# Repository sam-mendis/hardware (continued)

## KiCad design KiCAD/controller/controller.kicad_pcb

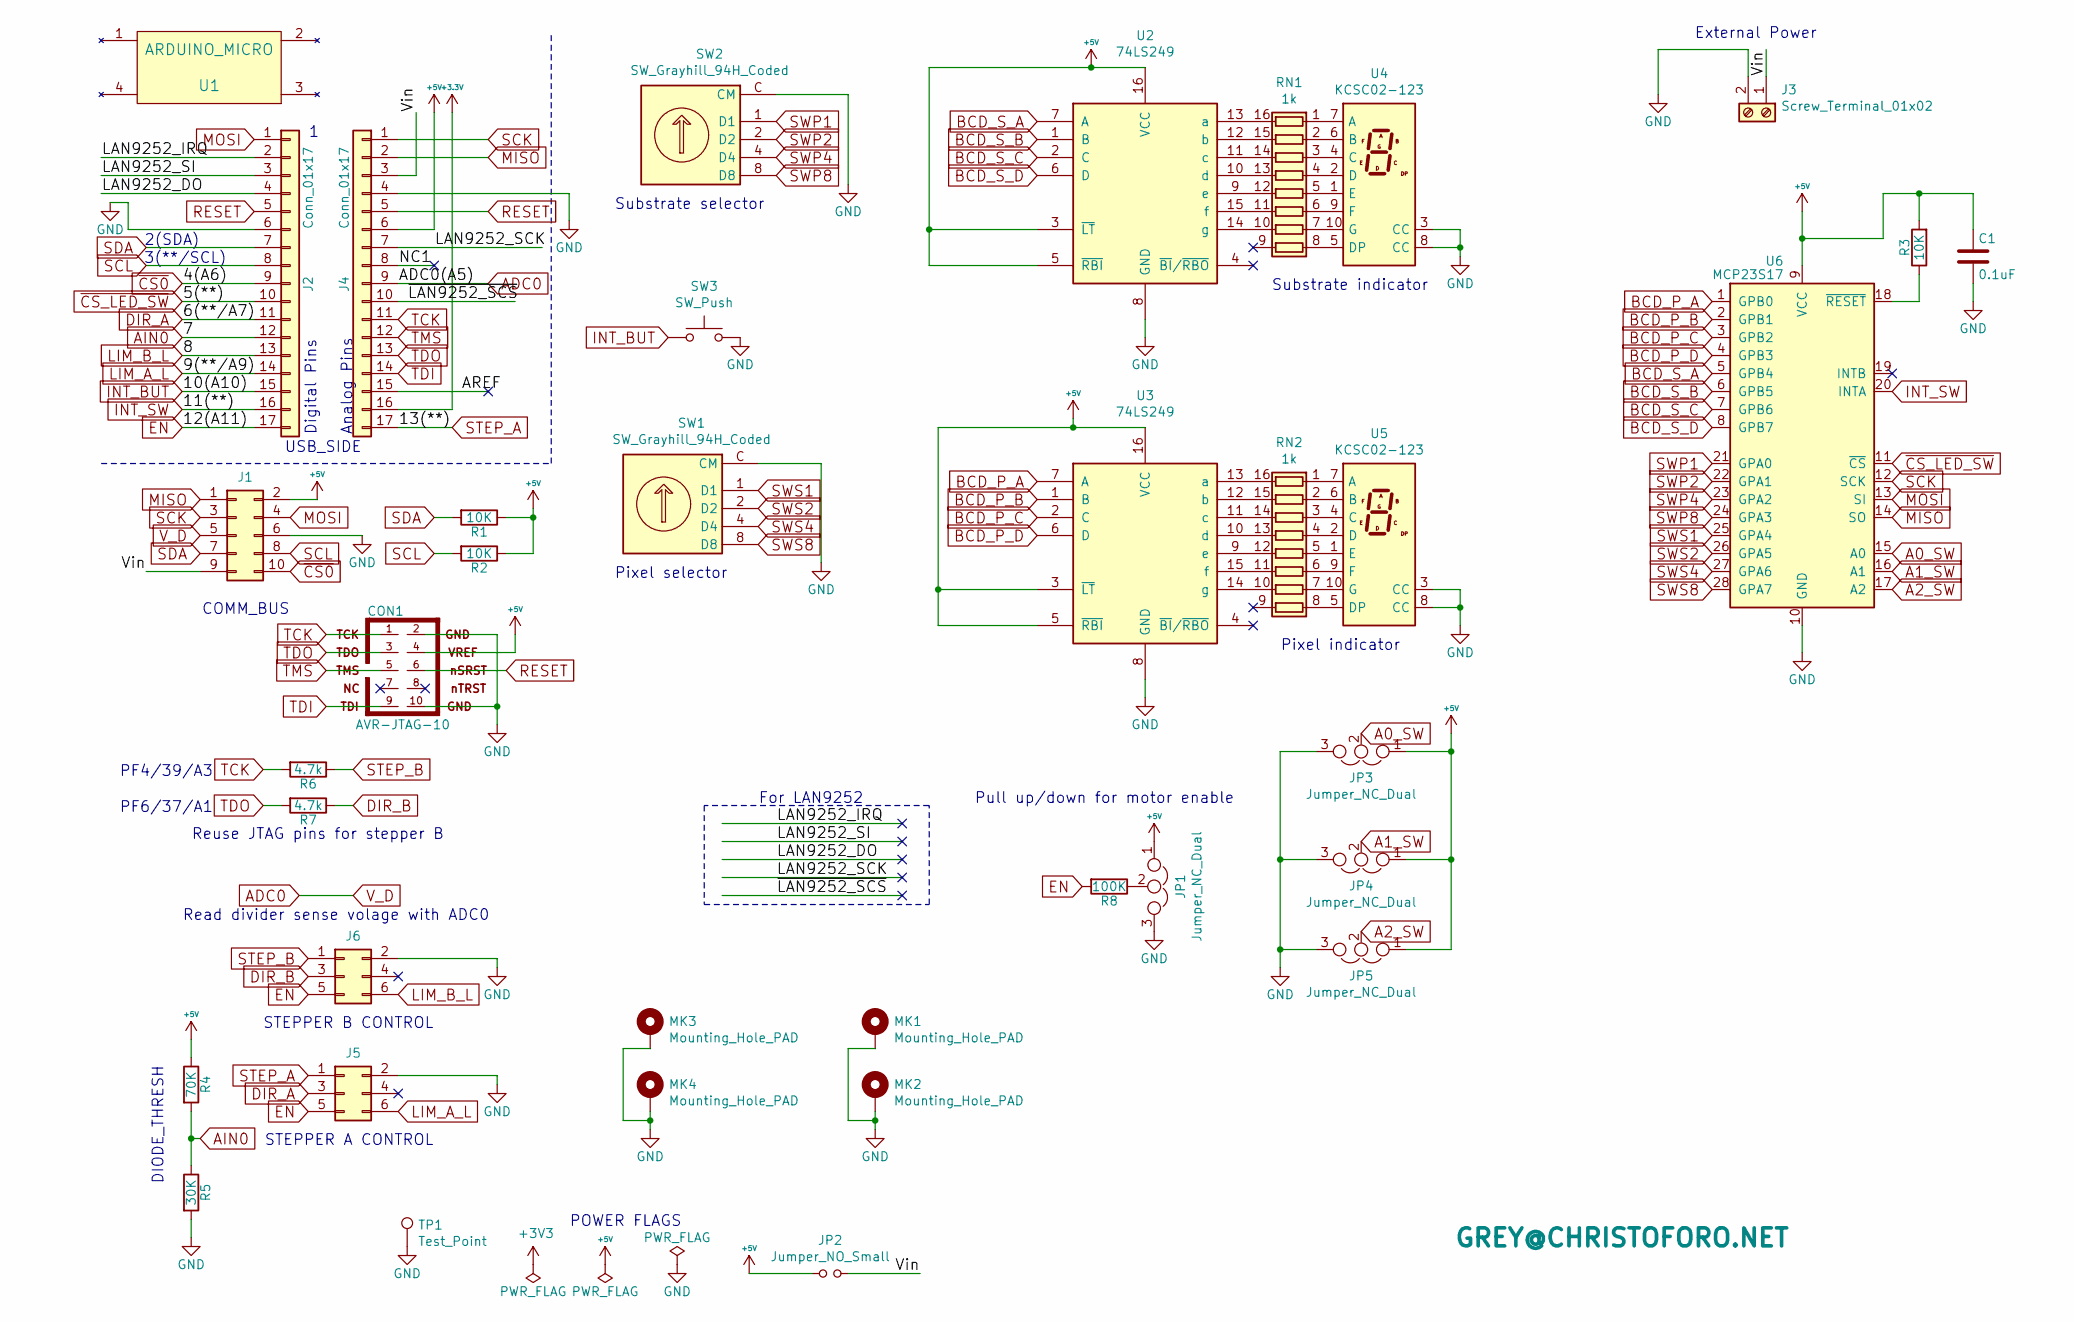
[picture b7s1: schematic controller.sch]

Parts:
C1: 0.1uF; C_0805_HandSoldering
CON1: AVR-JTAG-10; Multicomp_MC9A12-1034_2x05x2.54mm_Straight
J1: Conn_02x05_Counter_Clockwise; Pin_Header_Angled_2x05_Pitch2.54mm
J2, J4: Conn_01x17; Socket_Strip_Straight_1x17_Pitch2.54mm
J3: Screw_Terminal_01x02; PhoenixContact_MC-GF_02x3.50mm_Angled_ThreadedFlange_MountH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
J5, J6: Conn_02x03_Odd_Even; Pin_Header_Angled_2x03_Pitch2.54mm
JP1, JP3, JP4, JP5: Jumper_NC_Dual; GS3
JP2: Jumper_NO_Small; GS2
L1: GREY@CHRISTOFORO.NET; logo
MK1, MK2, MK3, MK4: Mounting_Hole_PAD; MountingHole_2.2mm_M2_Pad
R1, R2, R3: 10K; R_0805_HandSoldering
R4: 70K; R_0805_HandSoldering
R5: 30K; R_0805_HandSoldering
R6, R7: 4.7k; R_0805_HandSoldering
R8: 100K; R_0805_HandSoldering
RN1, RN2: 1k; DIP-16_W7.62mm
SW1, SW2: SW_Grayhill_94H_Coded; Grayhill_94H; farnellCode 1608126+1082532
SW3: SW_Push; SW_PUSH_6mm
TP1: Test_Point; Test_Point_S1751-46R
U1: ARDUINO_MICRO; arduino_micro
U2, U3: 74LS249; DIP-16_W7.62mm
U4, U5: KCSC02-123
U6: MCP23S17; DIP-28_W7.62mm

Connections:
+5V: C1.1, CON1.4, J1.2, J4.6, JP1.1, JP2.1, JP3.1, JP4.1, JP5.1, R1.1, R2.1, R3.2, R4.1, U2.3 (~LT), U2.5 (~RBI), U2.16 (VCC), U3.3 (~LT), U3.5 (~RBI), U3.16 (VCC), U6.9 (VCC)
/LAN9252_DO: J2.4
/LAN9252_IRQ: J2.2
/LAN9252_SCK: J4.7
/LAN9252_SI: J2.3
/Vin: J1.9, J3.1, J4.3, JP2.2
/~LAN9252_SCS: J4.10
A0_SW: JP3.2, U6.15 (A0)
A1_SW: JP4.2, U6.16 (A1)
A2_SW: JP5.2, U6.17 (A2)
ADC0: J1.5, J4.9
AIN0: J2.12, R4.2, R5.1
BCD_P_A: U3.7 (A), U6.1 (GPB0)
BCD_P_B: U3.1 (B), U6.2 (GPB1)
BCD_P_C: U3.2 (C), U6.3 (GPB2)
BCD_P_D: U3.6 (D), U6.4 (GPB3)
BCD_S_A: U2.7 (A), U6.5 (GPB4)
BCD_S_B: U2.1 (B), U6.6 (GPB5)
BCD_S_C: U2.2 (C), U6.7 (GPB6)
BCD_S_D: U2.6 (D), U6.8 (GPB7)
DIR_A: J2.11, J5.3
DIR_B: J6.3, R7.1
EN: J2.17, J5.5, J6.5, R8.2
GND: C1.2, CON1.2, CON1.10, J1.6, J2.6, J3.2, J4.4, J5.2, J6.2, JP1.3, JP3.3, JP4.3, JP5.3, MK1.1, MK2.1, MK3.1, MK4.1, R5.2, SW1.C (CM), SW2.C (CM), SW3.2, TP1.1, U2.8 (GND), U3.8 (GND), U4.3 (CC), U4.8 (CC), U5.3 (CC), U5.8 (CC), U6.10 (GND)
INT_BUT: J2.15, SW3.1
INT_SW: J2.16, U6.20 (INTA)
LIM_A_L: J2.14, J5.6
LIM_B_L: J2.13, J6.6
MISO: J1.1, J4.2, U6.14 (SO)
MOSI: J1.4, J2.1, U6.13 (SI)
unnamed: JP1.2, R8.1
unnamed: R3.1, U6.18 (~RESET)
unnamed: RN1.1 (R1.1), U4.7 (A)
unnamed: RN1.2 (R2.1), U4.6 (B)
unnamed: RN1.3 (R3.1), U4.4 (C)
unnamed: RN1.4 (R4.1), U4.2 (D)
unnamed: RN1.5 (R5.1), U4.1 (E)
unnamed: RN1.6 (R6.1), U4.9 (F)
unnamed: RN1.7 (R7.1), U4.10 (G)
unnamed: RN1.8 (R8.1), U4.5 (DP)
unnamed: RN1.10 (R7.2), U2.14 (g)
unnamed: RN1.11 (R6.2), U2.15 (f)
unnamed: RN1.12 (R5.2), U2.9 (e)
unnamed: RN1.13 (R4.2), U2.10 (d)
unnamed: RN1.14 (R3.2), U2.11 (c)
unnamed: RN1.15 (R2.2), U2.12 (b)
unnamed: RN1.16 (R1.2), U2.13 (a)
unnamed: RN2.1 (R1.1), U5.7 (A)
unnamed: RN2.2 (R2.1), U5.6 (B)
unnamed: RN2.3 (R3.1), U5.4 (C)
unnamed: RN2.4 (R4.1), U5.2 (D)
unnamed: RN2.5 (R5.1), U5.1 (E)
unnamed: RN2.6 (R6.1), U5.9 (F)
unnamed: RN2.7 (R7.1), U5.10 (G)
unnamed: RN2.8 (R8.1), U5.5 (DP)
unnamed: RN2.10 (R7.2), U3.14 (g)
unnamed: RN2.11 (R6.2), U3.15 (f)
unnamed: RN2.12 (R5.2), U3.9 (e)
unnamed: RN2.13 (R4.2), U3.10 (d)
unnamed: RN2.14 (R3.2), U3.11 (c)
unnamed: RN2.15 (R2.2), U3.12 (b)
unnamed: RN2.16 (R1.2), U3.13 (a)
RESET: CON1.6, J2.5, J4.5
SCK: J1.3, J4.1, U6.12 (SCK)
SCL: J1.8, J2.8, R2.2
SDA: J1.7, J2.7, R1.2
STEP_A: J4.17, J5.1
STEP_B: J6.1, R6.1
SWP1: SW2.1 (D1), U6.21 (GPA0)
SWP2: SW2.2 (D2), U6.22 (GPA1)
SWP4: SW2.4 (D4), U6.23 (GPA2)
SWP8: SW2.8 (D8), U6.24 (GPA3)
SWS1: SW1.1 (D1), U6.25 (GPA4)
SWS2: SW1.2 (D2), U6.26 (GPA5)
SWS4: SW1.4 (D4), U6.27 (GPA6)
SWS8: SW1.8 (D8), U6.28 (GPA7)
TCK: CON1.1, J4.11, R6.2
TDI: CON1.9, J4.14
TDO: CON1.3, J4.13, R7.2
TMS: CON1.5, J4.12
~CS0: J1.10, J2.9
~CS_LED_SW: J2.10, U6.11 (~CS)

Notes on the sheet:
POWER FLAGS
3(**/SCL)
2(SDA)
Digital Pins
Analog Pins
USB_SIDE
External Power
Read divider sense volage with ADC0
Substrate selector
Pixel selector
Substrate indicator
COMM_BUS
Pixel indicator
DIODE_THRESH
STEPPER A CONTROL
STEPPER B CONTROL
For LAN9252
Reuse JTAG pins for stepper B
Pull up/down for motor enable
PF4/39/A3
PF6/37/A1

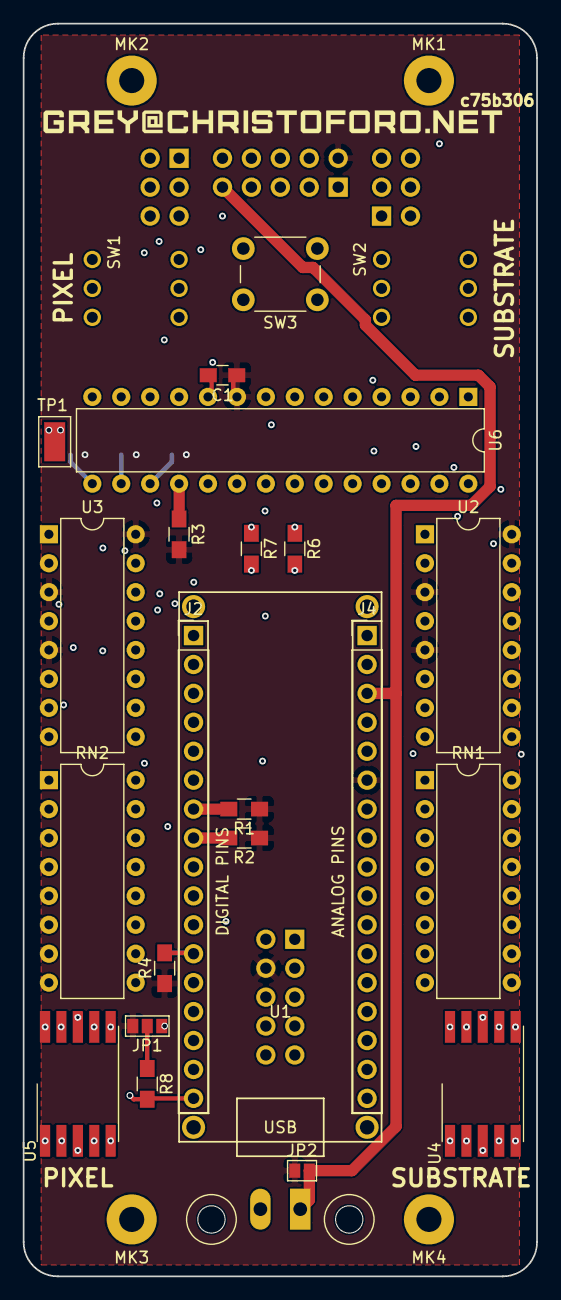
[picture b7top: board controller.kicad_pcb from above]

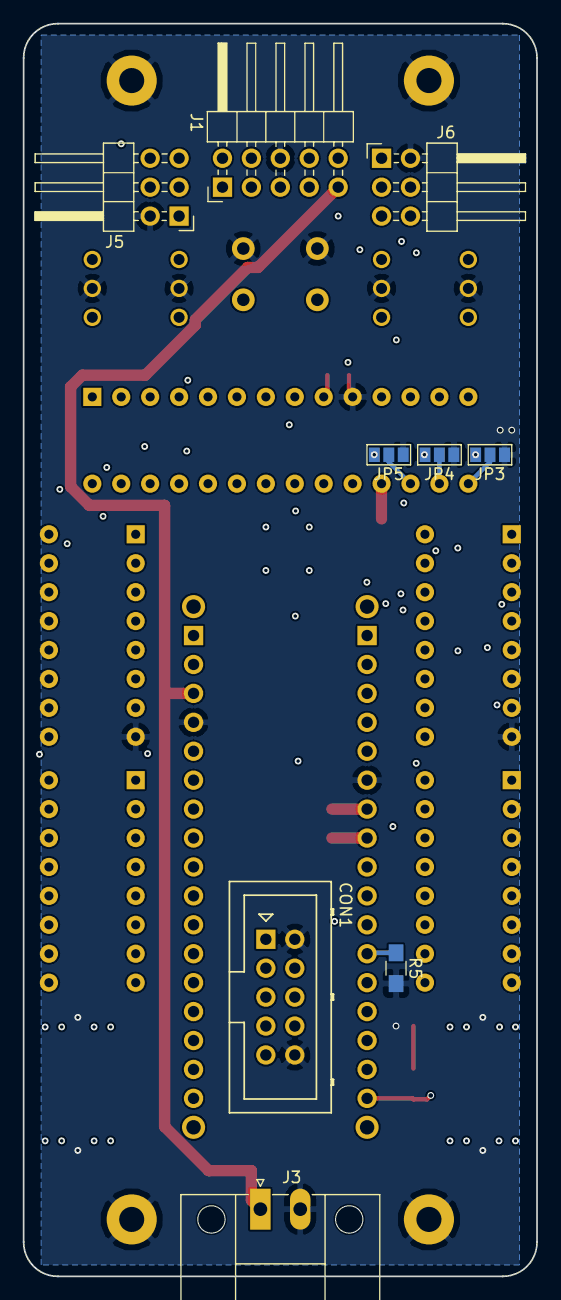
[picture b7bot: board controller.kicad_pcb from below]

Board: 4 copper layers, 45.1 x 110.0 mm, 38 parts (9 on the bottom side), 77 nets.

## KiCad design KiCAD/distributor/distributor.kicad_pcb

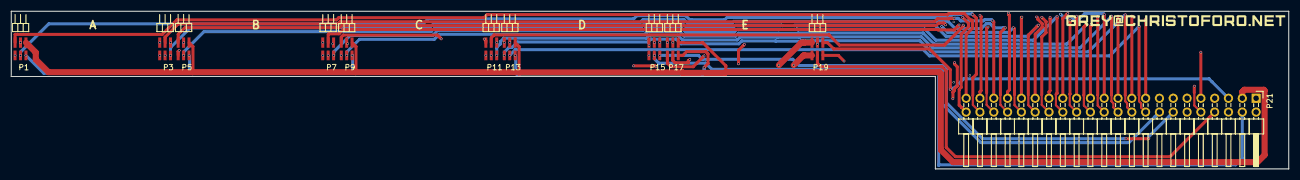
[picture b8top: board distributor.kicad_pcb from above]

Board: 4 copper layers, 235.0 x 29.0 mm, 11 parts (0 on the bottom side), 44 nets.

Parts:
P1, P3, P5, P7, P9, P11, P13, P15, P17, P19: CONN_02X03; FTMH-103-03-L-DH
P21: CONN_02X22; Pin_Header_Angled_2x22_Pitch2.54mm

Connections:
A0_I: P1.1, P21.43
A0_V: P1.2, P21.44
A2_I: P1.3, P21.41
A2_V: P1.4, P21.42
A4_I: P3.3, P21.39
A4_V: P3.4, P21.40
AR_I: P3.5, P21.37
AR_V: P3.6, P21.38
B0_I: P5.1, P21.35
B0_V: P5.2, P21.36
B2_I: P5.3, P21.33
B2_V: P5.4, P21.34
B4_I: P7.3, P21.31
B4_V: P7.4, P21.32
BR_I: P7.5, P21.29
BR_V: P7.6, P21.30
C0_I: P9.1, P21.27
C0_V: P9.2, P21.28
C2_I: P9.3, P21.25
C2_V: P9.4, P21.26
C4_I: P11.3, P21.23
C4_V: P11.4, P21.24
CR_I: P11.5, P21.21
CR_V: P11.6, P21.22
D0_I: P13.1, P21.19
D0_V: P13.2, P21.20
D2_I: P13.3, P21.17
D2_V: P13.4, P21.18
D4_I: P15.3, P21.15
D4_V: P15.4, P21.16
DR_I: P15.5, P21.13
DR_V: P15.6, P21.14
E0_I: P17.1, P21.11
E0_V: P17.2, P21.12
E2_I: P17.3, P21.9
E2_V: P17.4, P21.10
E4_I: P19.3, P21.7
E4_V: P19.4, P21.8
ER_I: P19.5, P21.5
ER_V: P19.6, P21.6
MISO: P1.6, P5.6, P9.6, P13.6, P17.6, P21.4
MOSI: P1.5, P5.5, P9.5, P13.5, P17.5, P21.3
SCL: P3.2, P7.2, P11.2, P15.2, P19.2, P21.2
SDA: P3.1, P7.1, P11.1, P15.1, P19.1, P21.1
